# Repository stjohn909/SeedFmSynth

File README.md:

# Seed FM Synth

## KiCad project for a multipurpose Daisy Seed PCB

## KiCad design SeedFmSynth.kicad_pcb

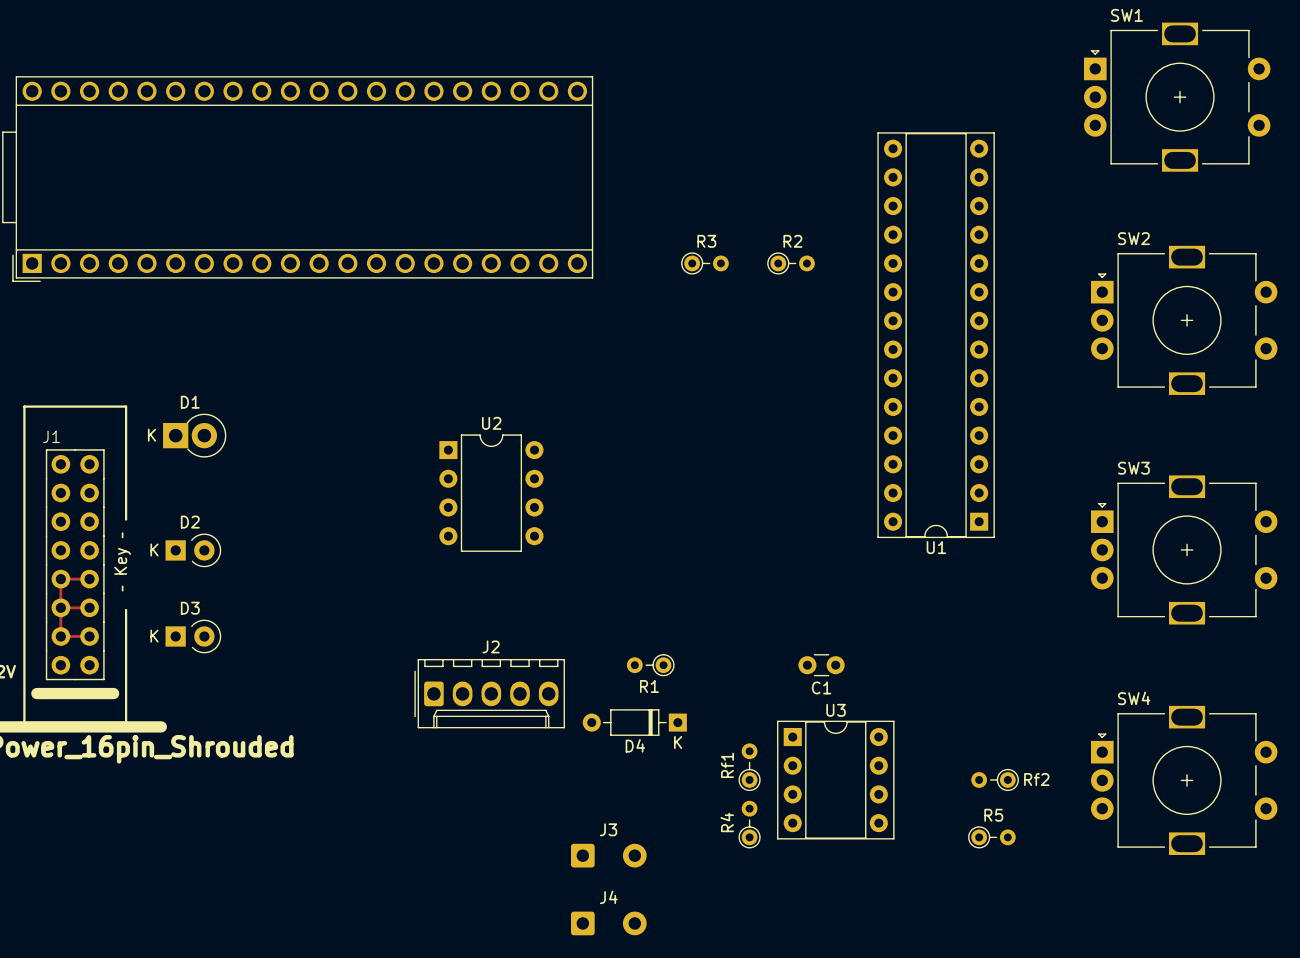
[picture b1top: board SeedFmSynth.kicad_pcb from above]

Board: 2 copper layers, 24 parts (0 on the bottom side), 34 nets.

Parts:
A1: Electrosmith_Daisy_Seed_Rev4; Electrosmith_Daisy_Seed
C1: 1u; C_Disc_D3.0mm_W1.6mm_P2.50mm
D1: D; D_DO-15_P2.54mm_Vertical_KathodeUp
D2, D3: D; D_A-405_P2.54mm_Vertical_KathodeUp
D4: 1N914; D_DO-35_SOD27_P7.62mm_Horizontal
J1: Eurorack_Power_16pin_Shrouded; Pins_2x08_2.54mm_TH_EuroPower_Shrouded
J2: MIDI IN; Molex_KK-254_AE-6410-05A_1x05_P2.54mm_Vertical
J3: EuroAudioOutR; SolderWire-0.5sqmm_1x02_P4.6mm_D0.9mm_OD2.1mm
J4: EuroAudioOutL; SolderWire-0.5sqmm_1x02_P4.6mm_D0.9mm_OD2.1mm
R1, R3: 220; R_Axial_DIN0204_L3.6mm_D1.6mm_P2.54mm_Vertical
R2: 470; R_Axial_DIN0204_L3.6mm_D1.6mm_P2.54mm_Vertical
R4, R5: 1k; R_Axial_DIN0204_L3.6mm_D1.6mm_P2.54mm_Vertical
Rf1, Rf2: 9.5k; R_Axial_DIN0204_L3.6mm_D1.6mm_P2.54mm_Vertical
SW1: Attack; RotaryEncoder_Alps_EC11E-Switch_Vertical_H20mm
SW2: Decay; RotaryEncoder_Alps_EC11E-Switch_Vertical_H20mm
SW3: Sustain; RotaryEncoder_Alps_EC11E-Switch_Vertical_H20mm
SW4: Release; RotaryEncoder_Alps_EC11E-Switch_Vertical_H20mm
U1: MCP23017_SS; DIP-28_W7.62mm_Socket
U2: 6N135; DIP-8_W7.62mm
U3: TL072; DIP-8_W7.62mm_Socket

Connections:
5V+: D1.2 (A), R3.1, U1.10 (VSS), U2.8
+5V: A1.39 (VIN), D1.1 (K), J1.5 (+12V), J1.6
+12V: D2.1 (K), J1.7 (12V), J1.8 (+12V)
-12V: D3.2 (A), J1.15 (-12V), J1.16
/Euro Audio/12V+: C1.1, U3.8 (V+)
/Euro Audio/Euro Out L: Rf2.2, U3.7
/Euro Audio/Euro Out R: Rf1.2, U3.1
/Euro Audio/GND: C1.2, U3.3 (+), U3.5 (+)
/INT A: A1.31 (SAI2_MCLK), U1.19 (INTB)
/INT B: A1.32 (SAI2_SD_B), U1.20 (INTA)
/UART 1 RX: R3.2, U2.6
GND: A1.20 (AGND), A1.40 (DGND), J1.9 (GND), J1.10 (GND), J1.11 (GND), J1.12 (GND), J1.13 (-12), J1.14 (-12V), R2.1, SW1.C, SW1.S1, SW2.C, SW2.S1, SW3.C, SW3.S1, SW4.C, SW4.S1, U1.9 (VDD), U2.5
unnamed: A1.12 (I2C1_SCL), U1.12 (SCK)
unnamed: A1.13 (I2C1_SDA), U1.13 (SDA)
unnamed: D4.2 (A), J2.5, U2.3
unnamed: D4.1 (K), R1.1, U2.2
unnamed: J1.1, J1.2
unnamed: J1.3, J1.4
unnamed: J2.4, R1.2
unnamed: R2.2, U2.7
unnamed: SW4.A, U1.25 (GPA4)
unnamed: SW3.A, U1.26 (GPA5)
unnamed: SW2.A, U1.27 (GPA6)
unnamed: SW1.A, U1.28 (GPA7)
unnamed: SW4.S2, U1.1 (GPB0)
unnamed: SW3.S2, U1.2 (GPB1)
unnamed: SW2.S2, U1.3 (GPB2)
unnamed: SW1.S2, U1.4 (GPB3)
unnamed: SW4.B, U1.5 (GPB4)
unnamed: SW3.B, U1.6 (GPB5)
unnamed: SW2.B, U1.7 (GPB6)
unnamed: SW1.B, U1.8 (GPB7)
unnamed: R4.2, Rf1.1, U3.2 (-)
unnamed: R5.1, Rf2.1, U3.6 (-)

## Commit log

2026-01-07 Ignore and readme
2026-01-07 Update to KiCad 9
2026-01-08 update to 9.07 on mac
2026-01-10 Organizing KiCad project before adding cpp source
2026-01-10 Moving latest kicad backup
